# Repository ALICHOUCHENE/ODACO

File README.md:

# ODACO

### Description : 

ODACO consists of a personnal smart trainer that allows the user to live the whole experience of a private trainning session with adapted programs, posture detection and correction, voice commands and interactions with a simple and easy interface.

### My contributions : 

- Developing a voice assistant from scratch using python and Snowboy Hotword Detection toolkit.
 
- Integration of the voice assistant algorithm on Raspberry Pi while performing a Multithreading technique.
 
- Creation of the user interface Nvidia Jetson Nano board using python.

- Creation of gadgets to mesure biometric data of the user using Atmega328P microcontroller.

- Assuring the communication among different compartments via Bluetooth, socket communication and radio frequencies.

- Designing of all the electronic circuits of the system, based on AVR microcontrollers, with KiCad.

### Hardware : 

- **THE BOX :**

The box is the main part of the system.

It's based on 3 embedded boards :

- NVIDIA Jetson nano running an AI algorithm wich detect and analyse the humain posture.

- Raspberry Pi4 running the voice assistant algorithm.

- Arduino nano to communicate with the remote control, bandes and the posture belt.

## Band :

Those bandes will vibrate when the person make a wrong performance. 
Its circuit is based on : 

- Atmel microcontroller (Atmega328p) running at 8 MHz.

- RF433 radio receiver.

- Vibrator motor.

- Battery management system for 3.7v lipo battery.

- PCB View : 

- Board 3D view : 

## Belt :

This gadget is used to get biometric data of the user and send it to the Box: 
Its circuit is based on : 

- Atmel microcontroller (Atmega328p) running at 16 MHz.

- HC-06 Bluetooth Module.

- MAX30100 biometric (SPO2, Heart rate and Temperature .

- Battery management system for 3.7v lipo battery.

- Step Up Boost circuit (3.7V to 5V).

- PCB View : 

- Board 3D view : 

## Stay Safe :

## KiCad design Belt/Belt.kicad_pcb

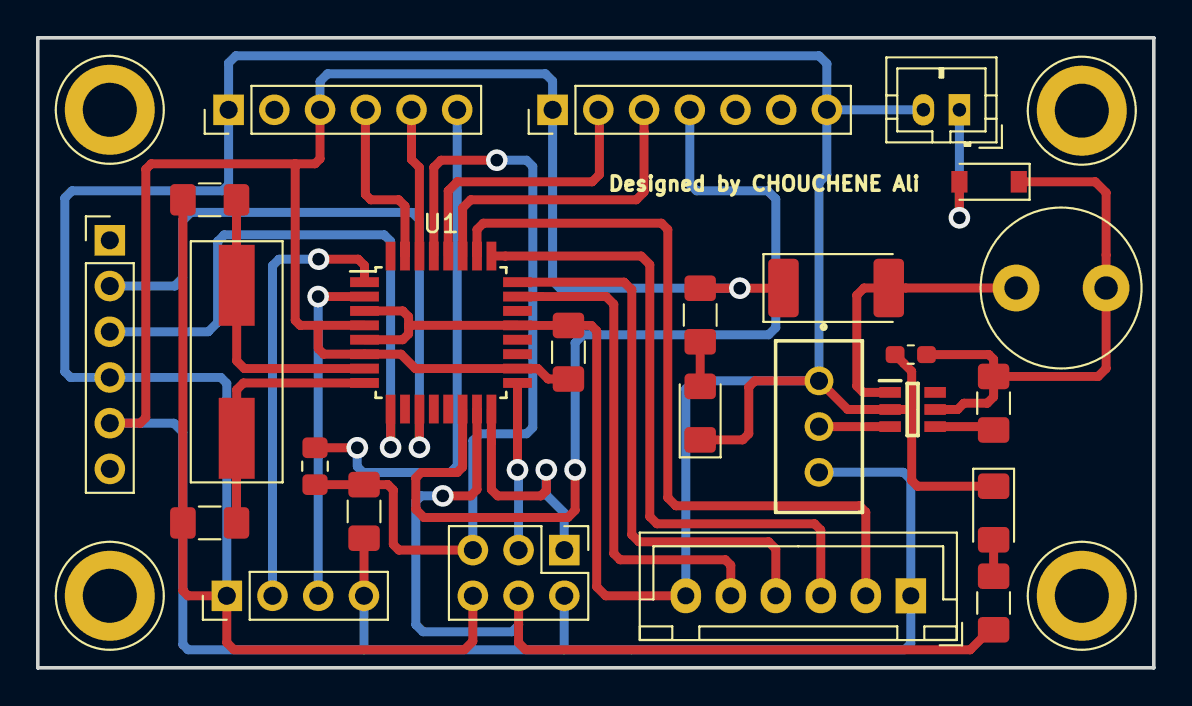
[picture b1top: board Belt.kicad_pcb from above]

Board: 2 copper layers, 62.0 x 35.0 mm, 25 parts (0 on the bottom side), 29 nets.

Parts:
BT1: Battery_Cell; JST_PH_B2B-PH-K_1x02_P2.00mm_Vertical
C1, C2: 22pF; C_1206_3216Metric_Pad1.42x1.75mm_HandSolder
C3: 100nF; C_1206_3216Metric_Pad1.42x1.75mm_HandSolder
C4: 10uF; C_0603_1608Metric_Pad1.05x0.95mm_HandSolder
C5: 100nF; C_0805_2012Metric_Pad1.15x1.40mm_HandSolder
D1: MBR1020VL; D_SOD-123
D2, D3: LED_ALT; LED_1206_3216Metric_Pad1.42x1.75mm_HandSolder
D4: FML340A-W; LED_2512_6332Metric_Castellated
J1: AVR-ISP-6; PinHeader_2x03_P2.54mm_Vertical
J2, J4: Conn_01x06_Female; PinHeader_1x06_P2.54mm_Vertical
J3: Conn_01x06_Female; JST_XH_B06B-XH-A_1x06_P2.50mm_Vertical
J5: Conn_01x07_Male; PinHeader_1x07_P2.54mm_Vertical
J6: Conn_01x04_Female; PinHeader_1x04_P2.54mm_Vertical
L1: L_Small; L_Radial_D8.7mm_P5.00mm_Fastron_07HCP
R1, R3: 220R; R_1206_3216Metric_Pad1.42x1.75mm_HandSolder
R2: 10K; R_1206_3216Metric_Pad1.42x1.75mm_HandSolder
R4: 100K; R_1206_3216Metric_Pad1.42x1.75mm_HandSolder
U1: ATmega328-AU; TQFP-32_7x7mm_P0.8mm
U2: MT3608; SOT95P280X145-6N
VR1: 3296W-1-253LF; 3296W-1
Y1: 16MHz; Crystal_SMD_HC49-SD

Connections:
+3V8: C4.1, D1.1, L1.1, R4.2, U2.5
+5V: C3.1, D4.1, J1.2, J2.3, J3.1, J4.5, J5.1, J6.4, R2.1, R3.1, U1.4, U1.6, U1.18, VR1.3
A0: J3.5, U1.23
A1: J3.4, U1.24
A2: J3.3, U1.25
A3: J3.2, U1.26
FB: U2.3, VR1.2
GND: BT1.2, C1.1, C2.1, C3.2, C4.2, D2.1, D3.1, J1.6, J2.1, J3.6, J4.4, J5.7, J6.1, U1.3, U1.5, U1.21, U2.2, VR1.1
INT: J5.4, U1.14
MISO: J1.1, U1.16
MOSI: J1.4, R1.1, U1.15
unnamed: BT1.1, D1.2
unnamed: C5.2, J2.6
unnamed: D2.2, R3.2
unnamed: D3.2, R1.2
unnamed: D4.2, L1.2, U2.1
unnamed: R4.1, U2.4
RST: C5.1, J1.5, R2.2, U1.29
RXD: J2.5, U1.30
RX_HC05: J4.2, U1.11
SCK: J1.3, U1.17
SCL: J5.2, U1.28
SDA: J5.3, U1.27
SOFTRX: J6.2, U1.1
SOFTTX: J6.3, U1.2
TXD: J2.4, U1.31
TX_HC05: J4.3, U1.9
osc1: C1.2, U1.7, Y1.1
osc2: C2.2, U1.8, Y1.2

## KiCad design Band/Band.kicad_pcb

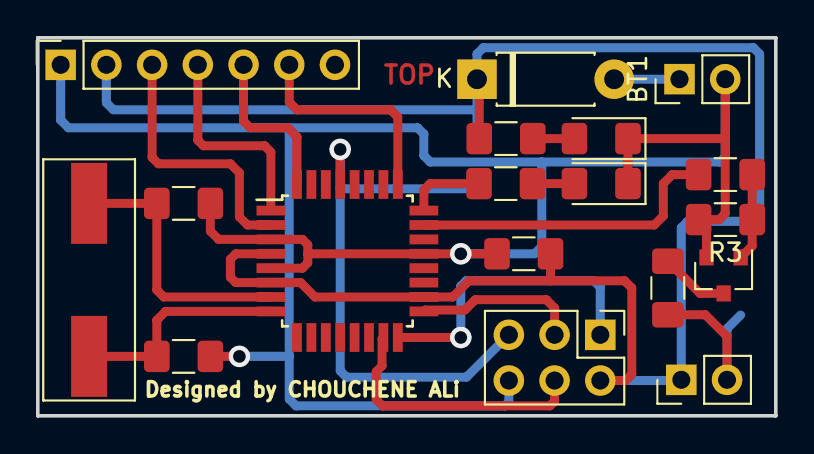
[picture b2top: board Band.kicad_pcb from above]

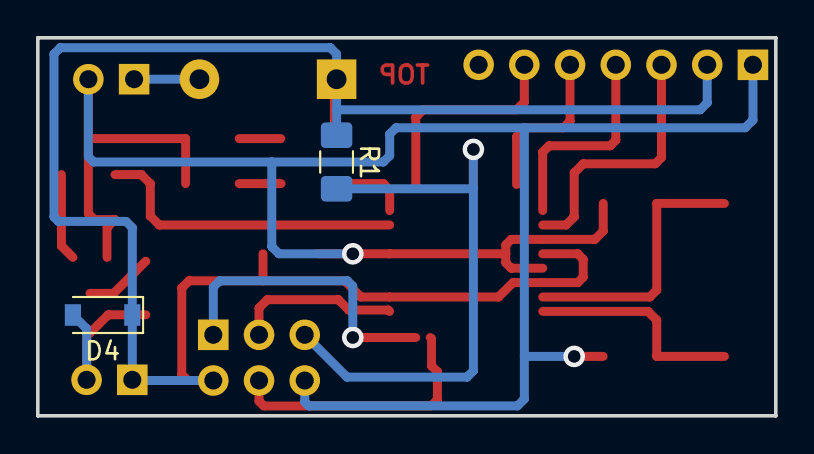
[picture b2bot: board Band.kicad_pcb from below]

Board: 2 copper layers, 41.0 x 21.0 mm, 20 parts (2 on the bottom side), 20 nets.

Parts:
BT1: Battery_Cell; PinHeader_1x02_P2.54mm_Vertical
C1: 100nF; C_1206_3216Metric_Pad1.42x1.75mm_HandSolder
C2, C3: 22pF; C_1206_3216Metric_Pad1.42x1.75mm_HandSolder
D1: 1N4001; D_DO-41_SOD81_P7.62mm_Horizontal
D2, D3: LED_ALT; LED_1206_3216Metric_Pad1.42x1.75mm_HandSolder
D4: 1N4001; D_SOD-123
J1: AVR-ISP-6; PinHeader_2x03_P2.54mm_Vertical
J3: Conn_01x07_Female; PinSocket_1x07_P2.54mm_Vertical
J4: Conn_01x02_Female; PinHeader_1x02_P2.54mm_Vertical
Q1: Q_NPN_BEC; SOT-23
R1: 10K; R_1206_3216Metric_Pad1.42x1.75mm_HandSolder
R2: 4K7; R_1206_3216Metric_Pad1.42x1.75mm_HandSolder
R3: 47K; R_1206_3216Metric_Pad1.42x1.75mm_HandSolder
R4: 100R; R_1206_3216Metric_Pad1.42x1.75mm_HandSolder
R5, R6: 220R; R_1206_3216Metric_Pad1.42x1.75mm_HandSolder
U1: ATmega328-AU; TQFP-32_7x7mm_P0.8mm
Y1: 16MHz; Crystal_SMD_HC49-SD

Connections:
+5V: C1.1, D1.1, D4.1, J1.2, J3.2, J4.1, R1.1, R5.1, U1.4, U1.6, U1.18
CMD: R2.2, U1.23
D0: J3.3, U1.2
D1: J3.4, U1.1
D2: J3.5, U1.32
D3: J3.6, U1.25
GND: BT1.2, C1.2, C2.1, C3.1, D2.1, D3.1, J1.6, J3.1, Q1.2, R3.2, U1.3, U1.5, U1.21
LED: R6.1, U1.24
MISO: J1.1, U1.16
MOSI: J1.4, U1.15
unnamed: BT1.1, D1.2
unnamed: D2.2, R5.2
unnamed: D3.2, R6.2
unnamed: Q1.1, R2.1, R3.1
unnamed: Q1.3, R4.2
RST: J1.5, R1.2, U1.29
SCK: J1.3, U1.17
Vibreur: D4.2, J4.2, R4.1
XTAL1: C2.2, U1.7, Y1.1
XTAL2: C3.2, U1.8, Y1.2

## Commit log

2021-04-23 Create Description
